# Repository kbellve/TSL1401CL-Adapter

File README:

Simple breakout adapter for the TSL1401CL, which is a replacement chip for TSL1401R-LF

The pads are larger than the footprint of the TSL1401CL so you can wick solder underneath the chip

Karl Bellve
Biomedical Imaging Group
Program in Molecular Medicine
University of Massachusetts Medical School

This board, including all the files required to produce the hardware, is licensed under a Creative Commons Attribution-ShareAlike 4.0 International License.

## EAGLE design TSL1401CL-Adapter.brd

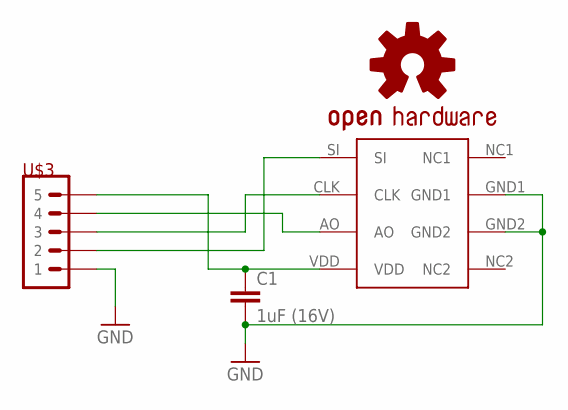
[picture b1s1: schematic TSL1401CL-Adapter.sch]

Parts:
C1: 1uF (16V); 0603-CAP
U$1: TSL1401CL
U$2: OSHW-LOGOM; OSHW-LOGO-M
U$3: M05; M05JST-PTH

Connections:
+5V: C1.1, U$1.VDD, U$3.P$5 (5)
AO: U$1.AO, U$3.P$4 (4)
CLK: U$1.CLK, U$3.P$3 (3)
GND: C1.2, U$1.GND1, U$1.GND2, U$3.P$1 (1)
SI: U$1.SI, U$3.P$2 (2)

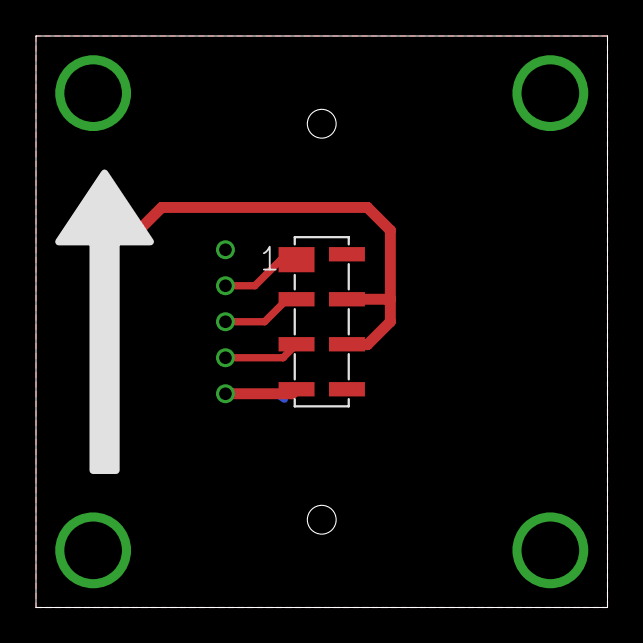
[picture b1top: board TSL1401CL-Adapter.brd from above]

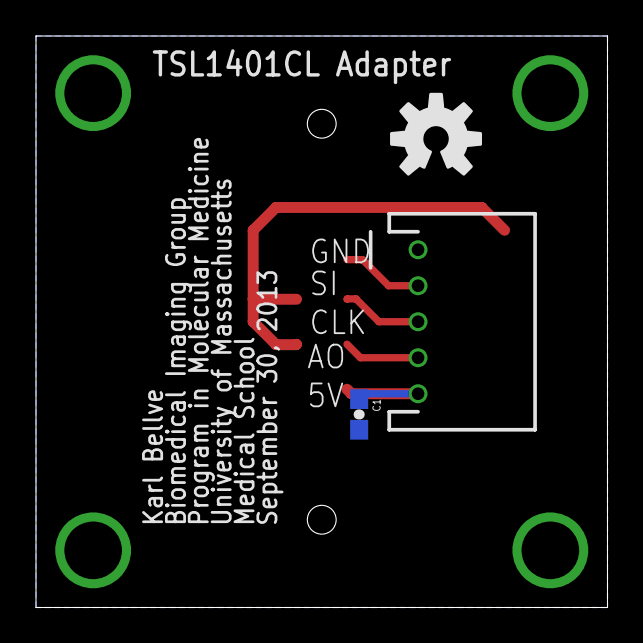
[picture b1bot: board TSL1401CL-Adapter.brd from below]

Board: 2 copper layers, 31.8 x 31.8 mm, 4 parts (3 on the bottom side), 5 nets.

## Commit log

2013-02-22 Changed holes size for shroud from 1.6 to 2.2mm
2013-03-28 Added 2x3 Shroud and made the board square with drill holes
2013-04-05 Modified to be used as a remote sensor to the pgFocus project
2013-04-11 Changed connector to JST 5 Pin
2013-04-24 Switched to 1/8" Via instead of a normal drill hole to help with grounding to a case
2013-05-01 Latest version sent to manufacturing
2013-09-30 Put the capacitor on the bottom, and adjusted position of connector to fit PT-LH011M from m12lenses.com
2015-07-13 Adding indiction of the top of the sensor

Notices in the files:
parts and their libraries:
SparkFun-Passives: Licensing: CC v3.0 Share-Alike You are welcome to use this library for commercial purposes.
